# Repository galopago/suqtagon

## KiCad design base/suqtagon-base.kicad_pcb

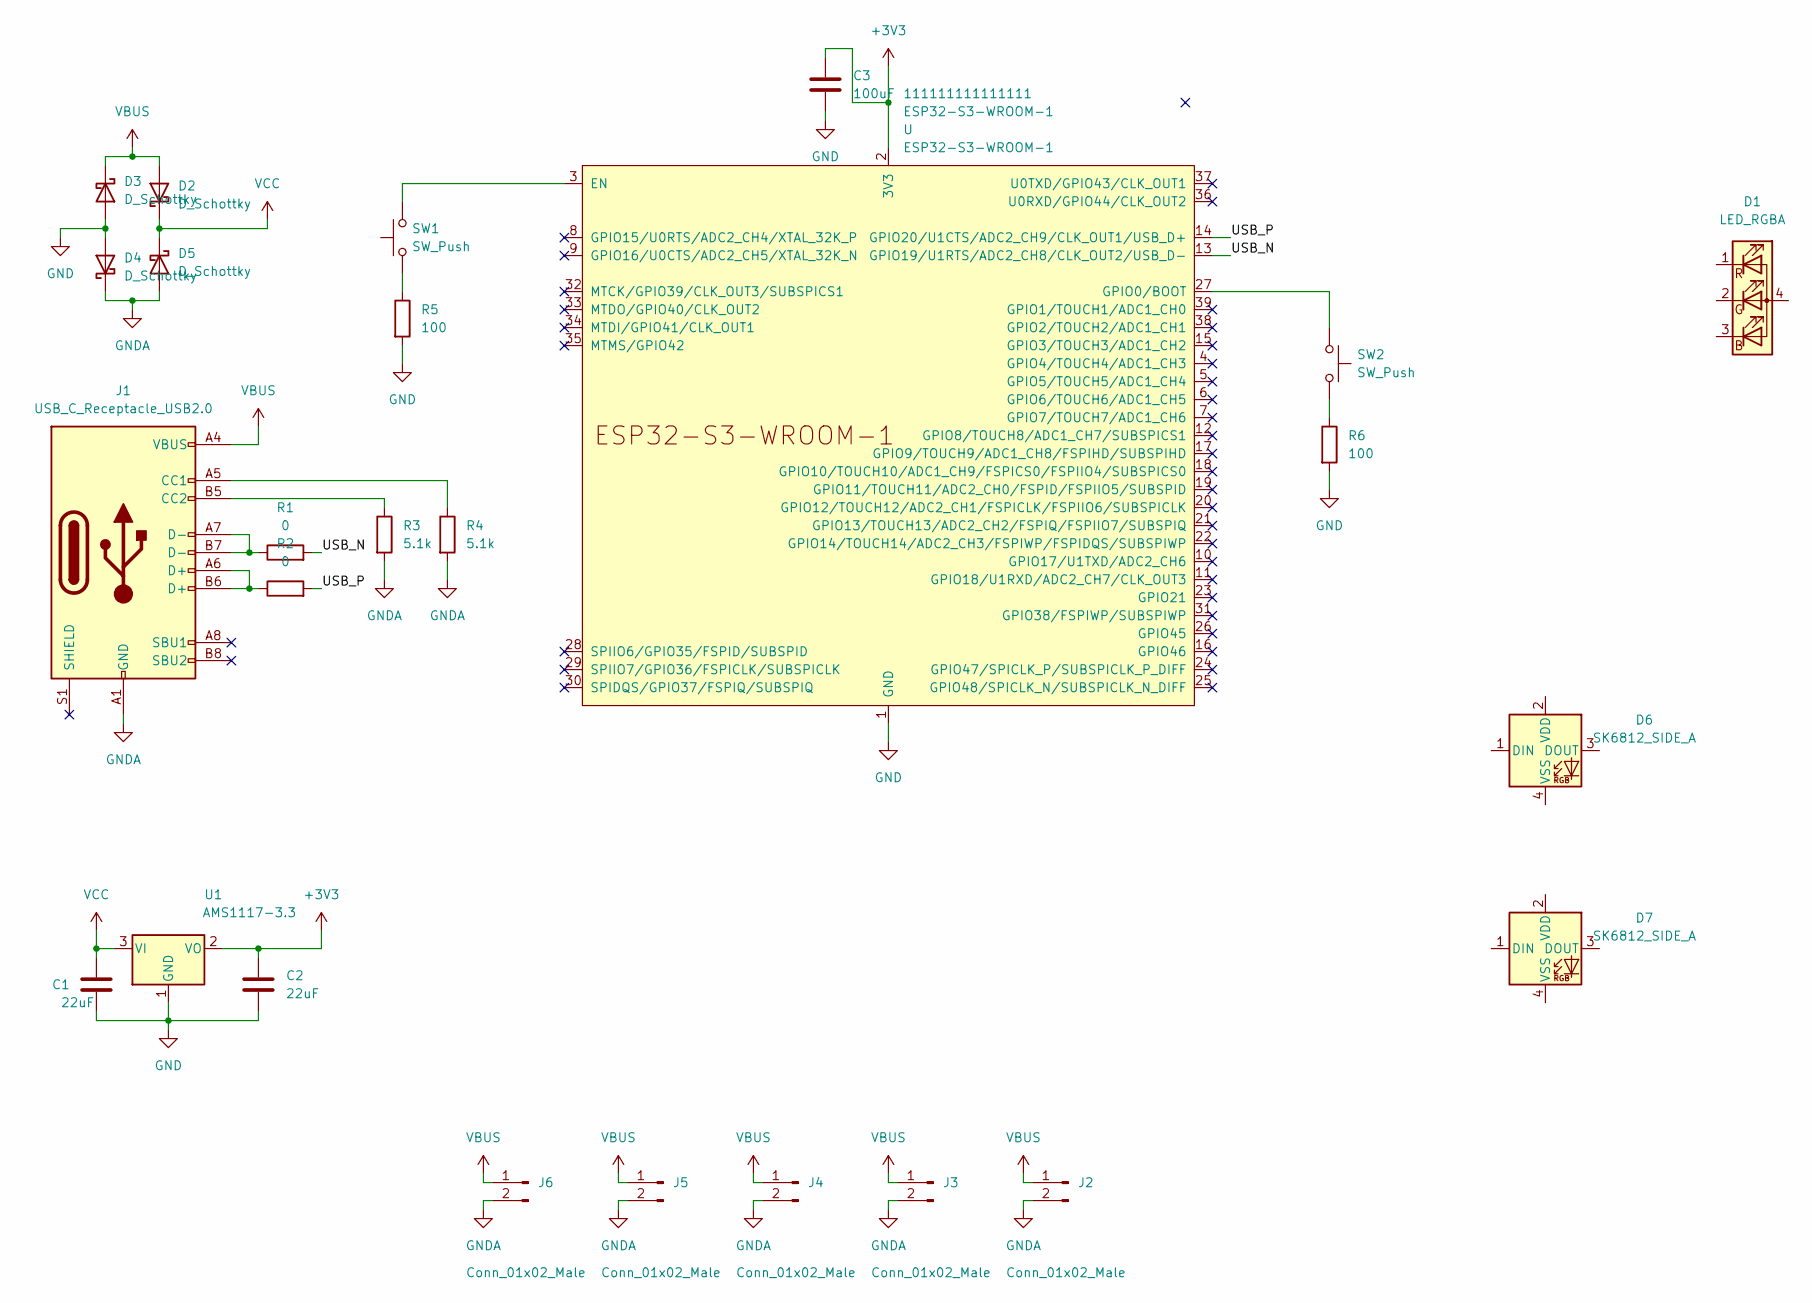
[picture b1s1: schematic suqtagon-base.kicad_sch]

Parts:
111111111111111: ESP32-S3-WROOM-1; ESP32-S3-WROOM-1U
C1, C2: 22uF; C_0805_2012Metric_Pad1.18x1.45mm_HandSolder
C3: 100uF; C_0805_2012Metric_Pad1.18x1.45mm_HandSolder
D1: LED_RGBA; LED_RGB_1210
D2, D3, D4, D5: D_Schottky; D_SMB
D6, D7: SK6812_SIDE_A; LED_SMD_SK6812_SIDE_A_4020_HandSolder
J1: USB_C_Receptacle_USB2.0; USB_C_Receptacle_HRO_TYPE-C-31-M-12
J2, J3, J4, J5, J6: Conn_01x02_Male; XH _PH_2P_1x02_P2.54mm_Horizontal
R1, R2: 0; R_0805_2012Metric_Pad1.20x1.40mm_HandSolder
R3, R4: 5.1k; R_0805_2012Metric_Pad1.20x1.40mm_HandSolder
R5, R6: 100; R_0805_2012Metric_Pad1.20x1.40mm_HandSolder
SW1, SW2: SW_Push; SW_Push_1P1T_NO_6x6mm_H9.5mm
U1: AMS1117-3.3; SOT-223-3_TabPin2

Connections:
+3V3: 111111111111111.2 (3V3), C2.1, C3.1, U1.2 (VO)
/USB_N: 111111111111111.13 (GPIO19/U1RTS/ADC2_CH8/CLK_OUT2/USB_D-), R1.2
/USB_P: 111111111111111.14 (GPIO20/U1CTS/ADC2_CH9/CLK_OUT1/USB_D+), R2.2
GND: 111111111111111.1 (GND), 111111111111111.40 (GND), 111111111111111.41 (GND), C1.2, C2.2, C3.2, D3.2 (A), D4.2 (A), R5.2, R6.2, U1.1 (GND)
GNDA: D4.1 (K), D5.2 (A), J1.A1 (GND), J1.A12 (GND), J1.B1 (GND), J1.B12 (GND), J2.2, J3.2, J4.2, J5.2, J6.2, R3.2, R4.2
unnamed: 111111111111111.3 (EN), SW1.2
unnamed: 111111111111111.27 (GPIO0/BOOT), SW2.1
unnamed: J1.A5 (CC1), R4.1
unnamed: J1.A6 (D+), J1.B6 (D+), R2.1
unnamed: J1.A7 (D-), J1.B7 (D-), R1.1
unnamed: J1.B5 (CC2), R3.1
unnamed: R5.1, SW1.1
unnamed: R6.1, SW2.2
VBUS: D2.2 (A), D3.1 (K), J1.A4 (VBUS), J1.A9 (VBUS), J1.B4 (VBUS), J1.B9 (VBUS), J2.1, J3.1, J4.1, J5.1, J6.1
VCC: C1.1, D2.1 (K), D5.1 (K), U1.3 (VI)

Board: 2 copper layers, 26 parts (0 on the bottom side), 15 nets, no tracks yet.

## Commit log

2024-02-26 started basic pcb hx template
2024-02-26 addded some mount holes
2024-03-01 more mounting holes
2024-03-02 all mount holes placed
2024-03-06 1204 smd side led footprint created
2024-03-11 advances in side board
2024-03-12 more advances in side board
2024-03-13 fixing wrong measurements on side pcb
2024-03-14 all traces routed
2024-03-14 added silk
2024-03-15 side single gerber
2024-03-15 side panel gerber
2024-03-18 populating some components in base
2024-03-19 added more esp components
2024-03-20 rotated screw blocks to allow flat screws
2024-03-24 started reverse led with pcb cut
2024-03-25 added smd connectors footprint
2024-03-27 started SK6812 side led footprint
2024-04-05 modfied polygon pad
2024-04-16 added second poly pad
2024-04-22 started adding hand solder footprints
2024-04-24 Fixed standard SK6812 SIDE A
2024-04-24 Fixed hand solder SK6812 SIDE A
2024-08-09 test background eb
